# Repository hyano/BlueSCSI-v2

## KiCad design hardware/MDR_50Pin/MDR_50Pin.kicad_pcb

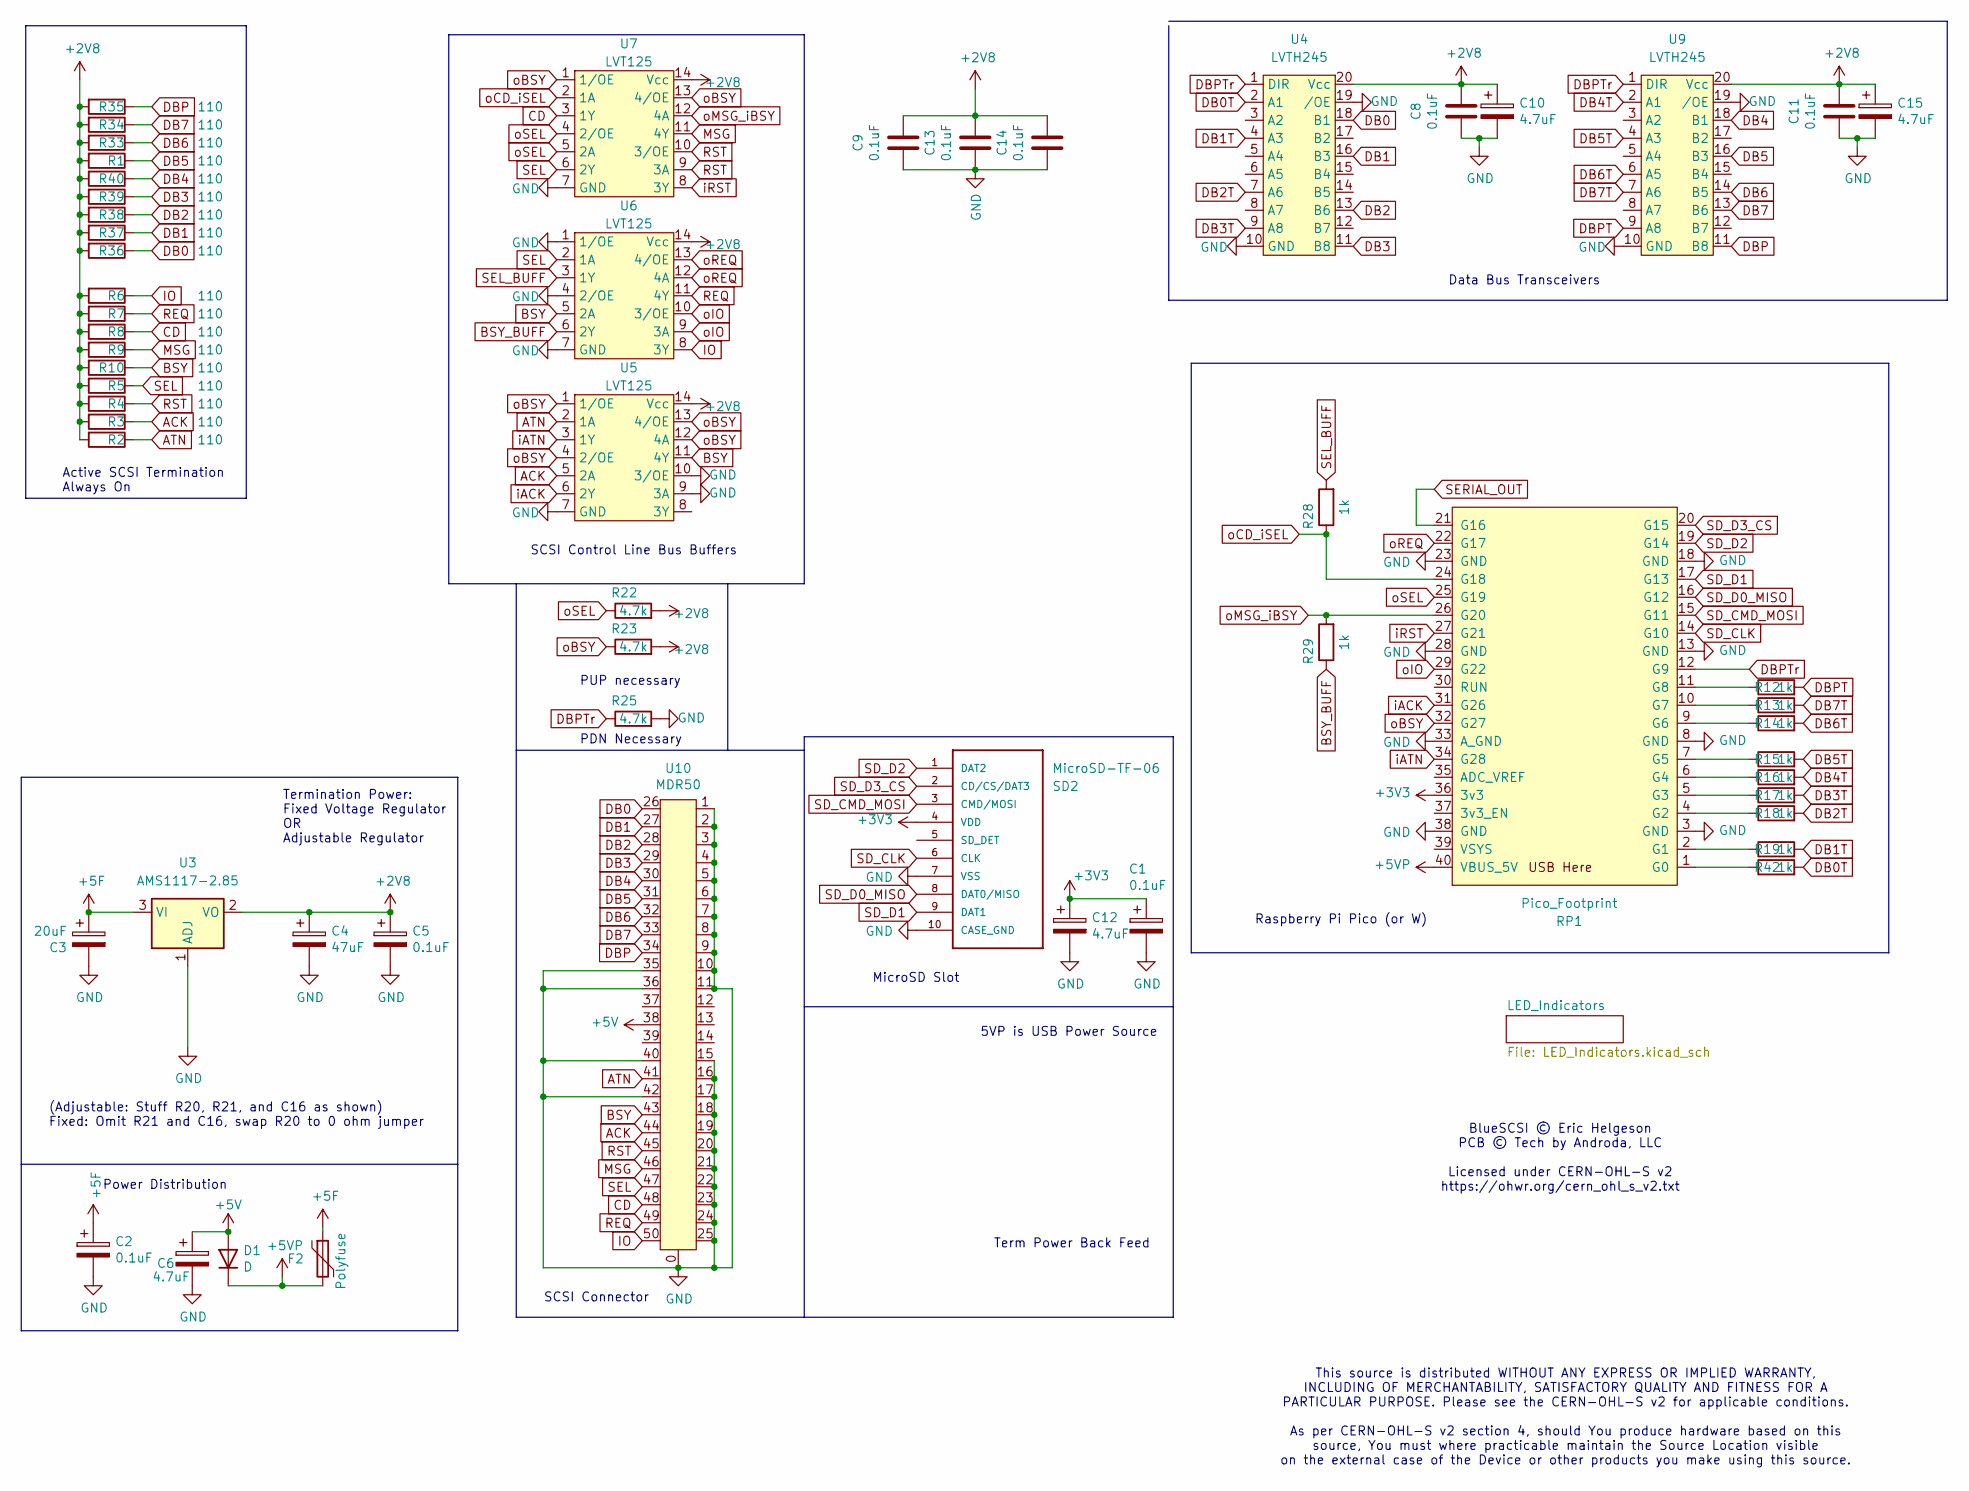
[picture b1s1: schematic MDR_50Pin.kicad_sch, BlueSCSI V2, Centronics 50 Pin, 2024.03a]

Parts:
C1, C2, C5, C8, C9, C11, C13, C14: 0.1uF; C_0603_1608Metric; LCSC Part # C14663
C3: 20uF; C_1206_3216Metric; LCSC Part # C5672
C4: 47uF; C_1206_3216Metric; LCSC Part # C96123
C6, C10, C12, C15: 4.7uF; C_0603_1608Metric; LCSC Part # C19666
D1: D; D_SMA; LCSC Part # C2480
F2: Polyfuse; Fuse_0805_2012Metric; LCSC Part # C883111
R1, R2, R3, R4, R5, R6, R7, R8, R9, R10, R33, R34, R35, R36, R37, R38, R39, R40: 110; R_0402_1005Metric; LCSC Part # C25078
R12, R13, R14, R15, R16, R17, R18, R19, R28, R29, R42: 1k; R_0402_1005Metric; LCSC Part # C11702
R22, R23, R25: 4.7k; R_0402_1005Metric; LCSC Part # C25900
RP1: Pico_Footprint; RPi_Pico_SMD
SD2: MicroSD-TF-06; TF-SMD_TF-06A; MANUFACTURER_PART_NUMBER C693844; LCSC Part # C693844
U3: AMS1117-2.85; SOT-223-3_TabPin2; LCSC Part # C14791
U4, U9: LVTH245; TSSOP-20_4.4x6.5mm_P0.65mm; LCSC Part # C2652121
U5, U6, U7: LVT125; TSSOP-14_4.4x5mm_P0.65mm; LCSC Part # C7042
U10: MDR50

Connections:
+2V8: C4.1, C5.1, C8.1, C9.2, C10.1, C11.1, C13.2, C14.2, C15.1, R1.2, R2.2, R3.2, R4.2, R5.2, R6.2, R7.2, R8.2, R9.2, R10.2, R22.2, R23.2, R33.2, R34.2, R35.2, R36.2, R37.2, R38.2, R39.2, R40.2, U3.2 (VO), U4.20 (Vcc), U5.14 (Vcc), U6.14 (Vcc), U7.14 (Vcc), U9.20 (Vcc)
+3V3: C1.1, C12.1, RP1.36 (3v3), SD2.4 (VDD); also elsewhere on the board
+5F: C2.1, C3.1, F2.1, U3.3 (VI); also elsewhere on the board
+5V: C6.1, D1.2 (A), U10.38
+5VP: D1.1 (K), F2.2, RP1.40 (VBUS_5V)
ACK: R3.1, U5.5 (2A), U10.44
ATN: R2.1, U5.2 (1A), U10.41
BSY: R10.1, U5.11 (4Y), U6.5 (2A), U10.43
BSY_BUFF: R29.1, U6.6 (2Y)
CD: R8.1, U7.3 (1Y), U10.48
DB0: R36.1, U4.18 (B1), U10.26
DB0T: R42.2, U4.2 (A1)
DB1: R37.1, U4.16 (B3), U10.27
DB1T: R19.2, U4.4 (A3)
DB2: R38.1, U4.13 (B6), U10.28
DB2T: R18.2, U4.7 (A6)
DB3: R39.1, U4.11 (B8), U10.29
DB3T: R17.2, U4.9 (A8)
DB4: R40.1, U9.18 (B1), U10.30
DB4T: R16.2, U9.2 (A1)
DB5: R1.1, U9.16 (B3), U10.31
DB5T: R15.2, U9.4 (A3)
DB6: R33.1, U9.14 (B5), U10.32
DB6T: R14.2, U9.6 (A5)
DB7: R34.1, U9.13 (B6), U10.33
DB7T: R13.2, U9.7 (A6)
DBP: R35.1, U9.11 (B8), U10.34
DBPT: R12.2, U9.9 (A8)
DBPTr: R25.1, RP1.12 (G9), U4.1 (DIR), U9.1 (DIR)
GND: C1.2, C2.2, C3.2, C4.2, C5.2, C6.2, C8.2, C9.1, C10.2, C11.2, C12.2, C13.1, C14.1, C15.2, R25.2, RP1.3 (GND), RP1.8 (GND), RP1.13 (GND), RP1.18 (GND), RP1.23 (GND), RP1.28 (GND), RP1.33 (A_GND), RP1.38 (GND), SD2.7 (VSS), SD2.10 (CASE_GND), U3.1 (ADJ), U4.10 (GND), U4.19 (/OE), U5.7 (GND), U5.9 (3A), U5.10 (3/OE), U6.1 (1/OE), U6.4 (2/OE), U6.7 (GND), U7.7 (GND), U9.10 (GND), U9.19 (/OE), U10.0, U10.1, U10.2, U10.3, U10.4, U10.5, U10.6, U10.7, U10.8, U10.9, U10.10, U10.11, U10.15, U10.16, U10.17, U10.18, U10.19, U10.20, U10.21, U10.22, U10.23, U10.24, U10.25, U10.35, U10.36, U10.40, U10.42; also elsewhere on the board
IO: R6.1, U6.8 (3Y), U10.50
MSG: R9.1, U7.11 (4Y), U10.46
unnamed: R42.1, RP1.1 (G0)
unnamed: R19.1, RP1.2 (G1)
unnamed: R18.1, RP1.4 (G2)
unnamed: R17.1, RP1.5 (G3)
unnamed: R16.1, RP1.6 (G4)
unnamed: R15.1, RP1.7 (G5)
unnamed: R14.1, RP1.9 (G6)
unnamed: R13.1, RP1.10 (G7)
unnamed: R12.1, RP1.11 (G8)
REQ: R7.1, U6.11 (4Y), U10.49
RST: R4.1, U7.9 (3A), U7.10 (3/OE), U10.45
SD_CLK: RP1.14 (G10), SD2.6 (CLK)
SD_CMD_MOSI: RP1.15 (G11), SD2.3 (CMD/MOSI)
SD_D0_MISO: RP1.16 (G12), SD2.8 (DAT0/MISO)
SD_D1: RP1.17 (G13), SD2.9 (DAT1)
SD_D2: RP1.19 (G14), SD2.1 (DAT2)
SD_D3_CS: RP1.20 (G15), SD2.2 (CD/CS/DAT3)
SEL: R5.1, U6.2 (1A), U7.6 (2Y), U10.47
SEL_BUFF: R28.2, U6.3 (1Y)
SERIAL_OUT: RP1.21 (G16)
iACK: RP1.31 (G26), U5.6 (2Y)
iATN: RP1.34 (G28), U5.3 (1Y)
iRST: RP1.27 (G21), U7.8 (3Y)
oBSY: R23.1, RP1.32 (G27), U5.1 (1/OE), U5.4 (2/OE), U5.12 (4A), U5.13 (4/OE), U7.1 (1/OE), U7.13 (4/OE); also elsewhere on the board
oCD_iSEL: R28.1, RP1.24 (G18), U7.2 (1A)
oIO: RP1.29 (G22), U6.9 (3A), U6.10 (3/OE)
oMSG_iBSY: R29.2, RP1.26 (G20), U7.12 (4A)
oREQ: RP1.22 (G17), U6.12 (4A), U6.13 (4/OE)
oSEL: R22.1, RP1.25 (G19), U7.4 (2/OE), U7.5 (2A)

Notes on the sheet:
Data Bus Transceivers
Termination Power: Fixed Voltage Regulator OR Adjustable Regulator
Active SCSI Termination Always On
Raspberry Pi Pico (or W)
Power Distribution
MicroSD Slot
SCSI Control Line Bus Buffers
SCSI Connector
5VP is USB Power Source
PDN Necessary
BlueSCSI © Eric Helgeson PCB © Tech by Androda, LLC Licensed under CERN-OHL-S v2 https://ohwr.org/cern_ohl_s_v2.txt
This source is distributed WITHOUT ANY EXPRESS OR IMPLIED WARRANTY, INCLUDING OF MERCHANTABILITY, SATISFACTORY QUALITY AND FITNESS FOR A PARTICULAR PURPOSE. Please see the CERN-OHL-S v2 for applicable conditions. As per CERN-OHL-S v2 section 4, should You produce hardware based on this source, You 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
Term Power Back Feed
(Adjustable: Stuff R20, R21, and C16 as shown) Fixed: Omit R21 and C16, swap R20 to 0 ohm jumper
PUP necessary

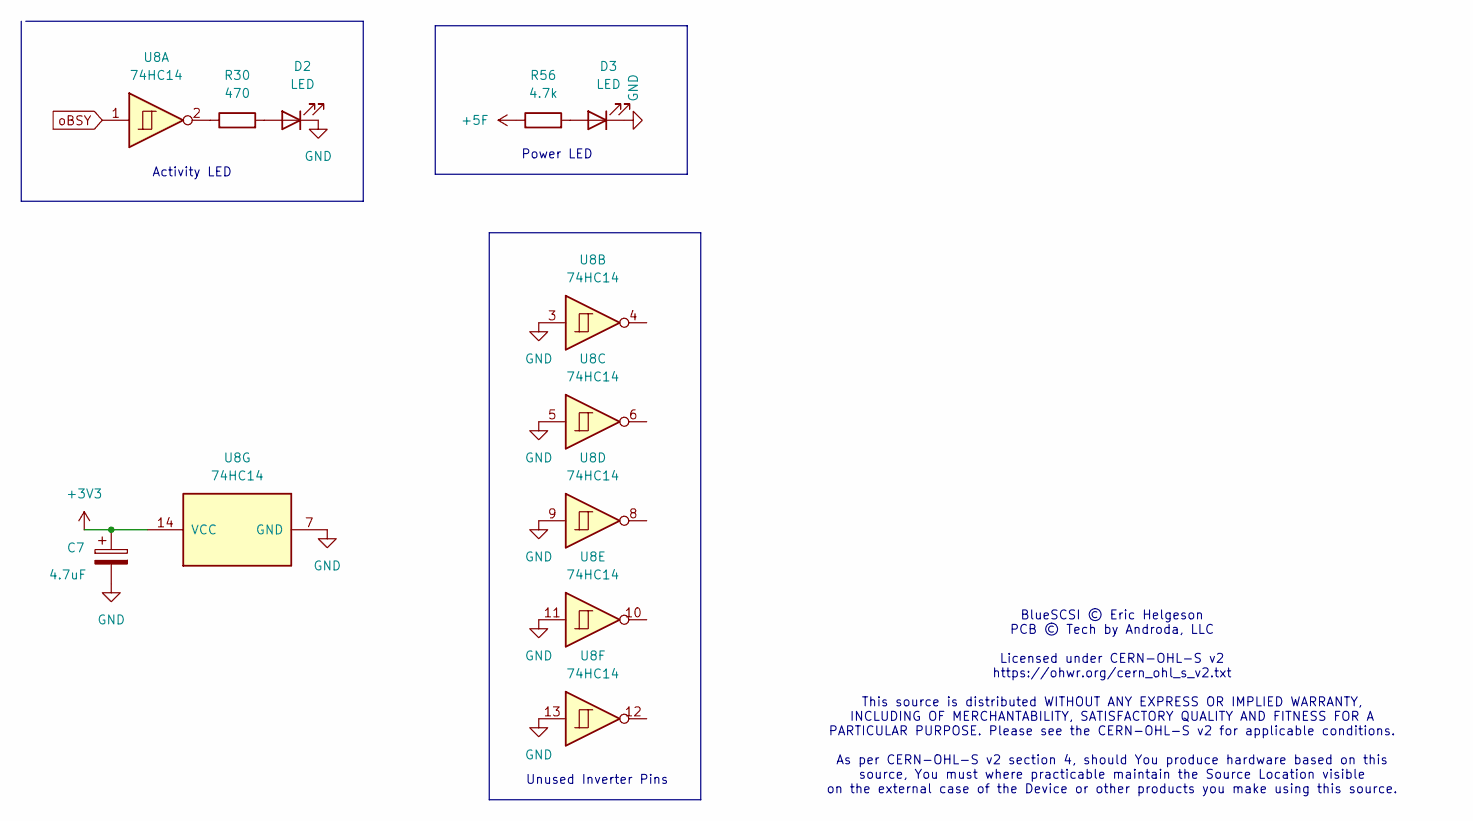
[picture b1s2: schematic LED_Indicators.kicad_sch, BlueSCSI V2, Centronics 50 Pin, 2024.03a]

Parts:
C7: 4.7uF; C_0805_2012Metric; LCSC Part # C1779
D2: LED; LED_0603_1608Metric; LCSC Part # C72041
D3: LED; LED_0603_1608Metric; LCSC Part # C2290
R30: 470; R_0402_1005Metric; LCSC Part # C25117
R56: 4.7k; R_0402_1005Metric; LCSC Part # C25900
U8: 74HC14; SOIC-14_3.9x8.7mm_P1.27mm; LCSC Part # C5605

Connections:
+3V3: C7.1, U8.14 (VCC); also elsewhere on the board
+5F: R56.1; also elsewhere on the board
GND: C7.2, D2.1 (K), D3.1 (K), U8.3, U8.5, U8.7 (GND), U8.9, U8.11, U8.13; also elsewhere on the board
unnamed: D2.2 (A), R30.2
unnamed: D3.2 (A), R56.2
unnamed: R30.1, U8.2
oBSY: U8.1; also elsewhere on the board

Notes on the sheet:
Power LED
Unused Inverter Pins
Activity LED
BlueSCSI © Eric Helgeson PCB © Tech by Androda, LLC Licensed under CERN-OHL-S v2 https://ohwr.org/cern_ohl_s_v2.txt This source is distributed WITHOUT ANY EXPRESS OR IMPLIED WARRANTY, INCLUDING OF MERCHANTABILITY, SATISFACTORY QUALITY AND FITNESS FOR A PARTICULAR PURPOSE. Please see the CERN-OHL-S 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

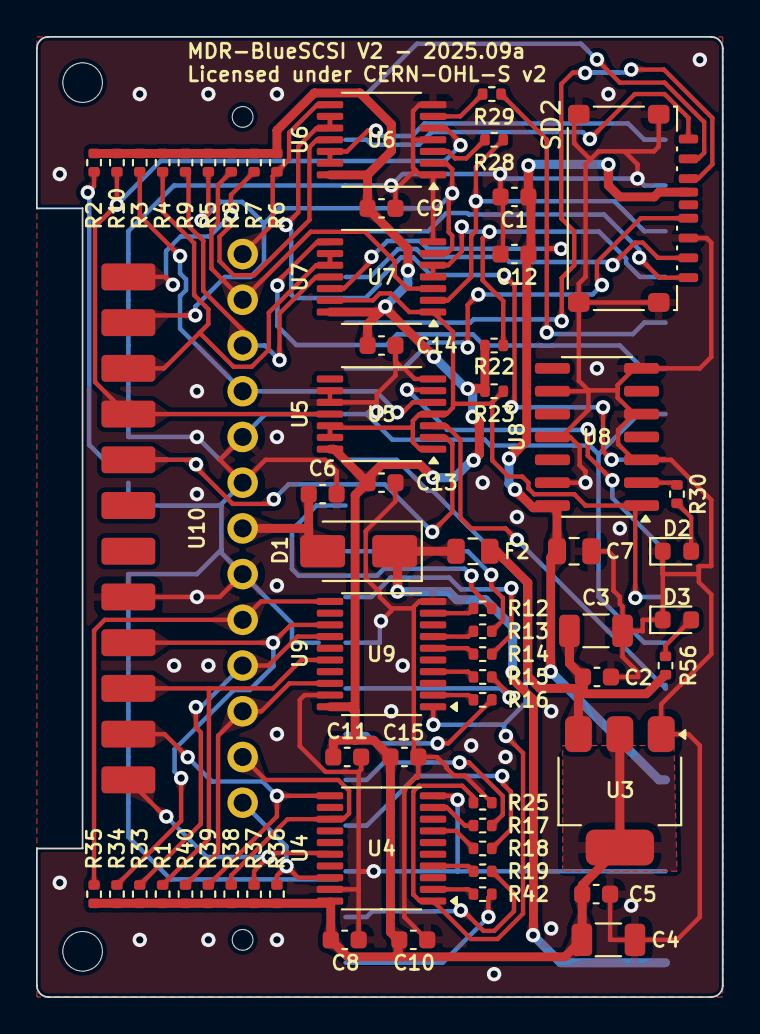
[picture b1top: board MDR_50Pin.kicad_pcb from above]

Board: 2 copper layers, 38.1 x 53.3 mm, 63 parts (1 on the bottom side), 63 nets.

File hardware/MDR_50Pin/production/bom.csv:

Designator,Footprint,Quantity,Value,LCSC Part #
"C1, C11, C13, C14, C2, C5, C8, C9",0603,8,0.1uF,C14663
"C10, C12, C15, C6",0603,4,4.7uF,C19666
C3,1206,1,20uF,C5672
C4,1206,1,47uF,C96123
C7,0805,1,4.7uF,C1779
D1,D_SMA,1,D,C2480
D2,0603,1,LED,C72041
D3,0603,1,LED,C2290
F2,0805,1,Polyfuse,C883111
"R1, R10, R2, R3, R33, R34, R35, R36, R37, R38, R39, R4, R40, R5, R6, R7, R8, R9",0402,18,110,C25078
"R12, R13, R14, R15, R16, R17, R18, R19, R28, R29, R42",0402,11,1k,C11702
"R22, R23, R25, R56",0402,4,4.7k,C25900
R30,0402,1,470,C25117
SD2,TF-SMD_TF-06A,1,MicroSD-TF-06,C693844
U3,SOT-223-3_TabPin2,1,AMS1117-2.85,C14791
"U4, U9",TSSOP-20_4.4x6.5mm_P0.65mm,2,LVTH245,C2652121
"U5, U6, U7",TSSOP-14_4.4x5mm_P0.65mm,3,LVT125,C7042
U8,SOIC-14_3.9x8.7mm_P1.27mm,1,74HC14,C5605

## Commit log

2025-09-07 copy from Centronics_50Pin
2025-09-07 rename from Centronics_50Pin
2025-09-15 latest design
2025-09-15 use tooling hole
2025-09-15 add *.FCBak
2025-09-15 increase screw hole depth
2025-09-20 widen LED window
2025-09-20 fixed unattached sketch
2025-09-23 minor modification
2025-10-05 reduce the size of nut hole
2025-10-05 Fixed circular dependencies
2025-10-05 update production data
